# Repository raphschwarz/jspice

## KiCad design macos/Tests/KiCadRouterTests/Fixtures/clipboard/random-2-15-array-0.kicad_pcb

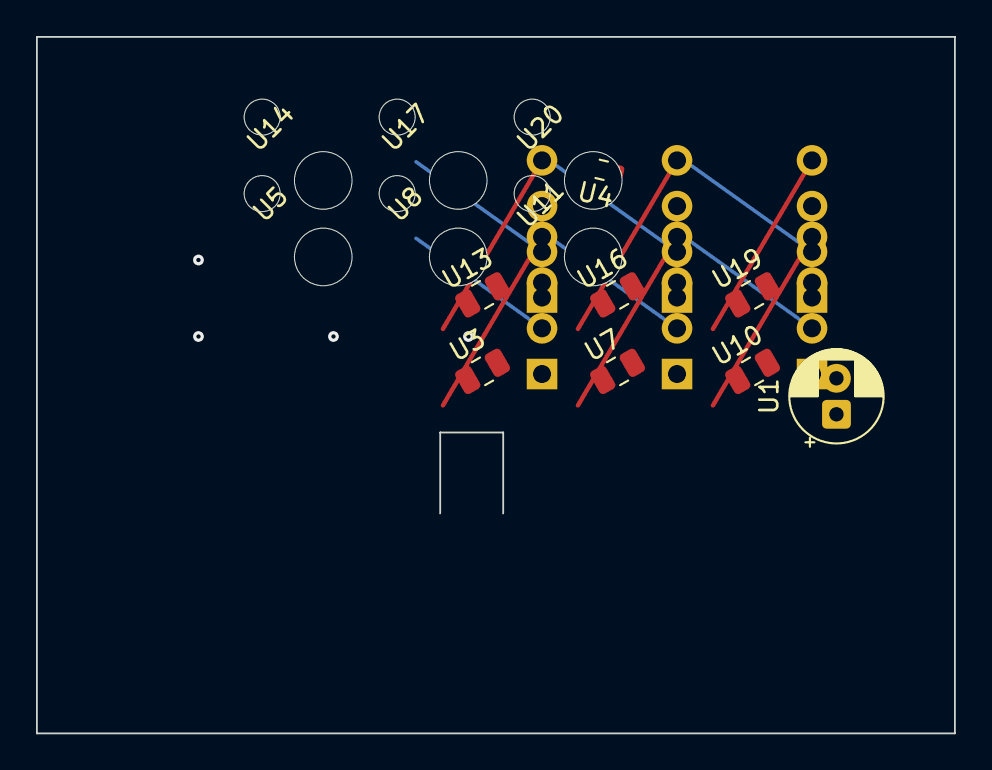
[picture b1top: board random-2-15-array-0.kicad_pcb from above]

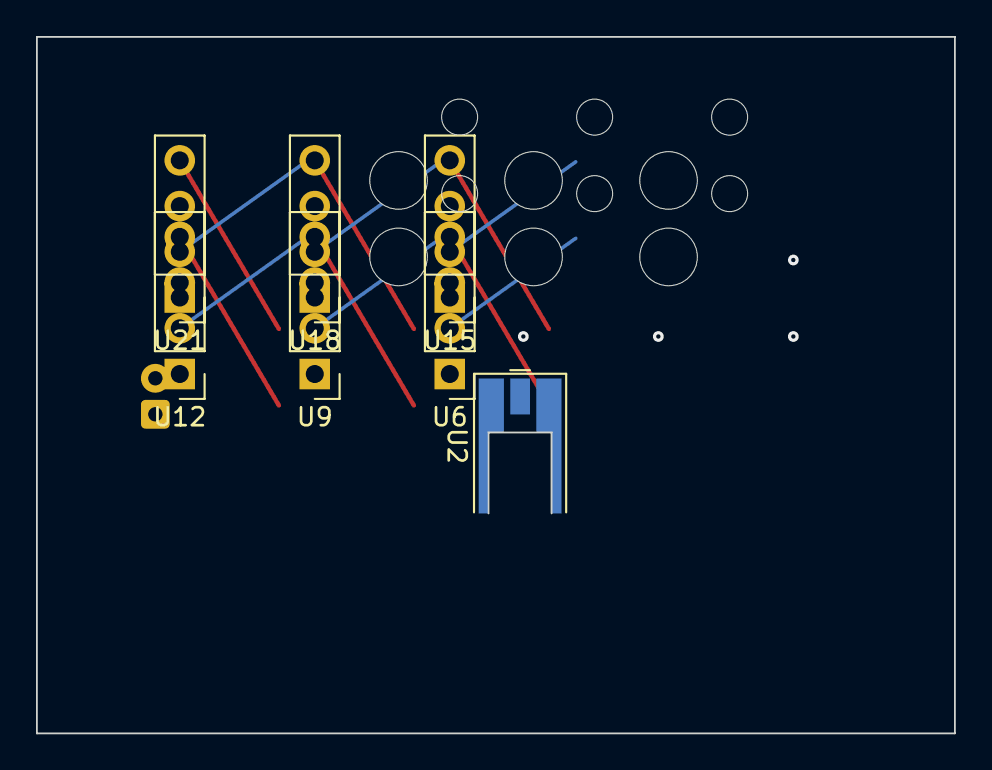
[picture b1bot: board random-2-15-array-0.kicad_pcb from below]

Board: 2 copper layers, 51.0 x 38.7 mm, 21 parts (7 on the bottom side), 2 nets.

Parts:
U1: CP_Radial_D5.0mm_P2.00mm
U2: MMCX_Molex_73415-0961_Horizontal_0.8mm-PCB
U3, U7, U10, U13, U16, U19: C_0805_2012Metric
U4: R_0603_1608Metric
U5, U8, U11, U14, U17, U20: MountingHole_3.2mm_M3
U6, U9, U12, U15, U18, U21: PinHeader_1x04_P2.54mm_Vertical

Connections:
N3: U1.1, U3.1, U6.1, U6.2, U7.1, U9.1, U9.2, U10.1, U12.1, U12.2, U13.1, U15.1, U15.2, U16.1, U18.1, U18.2, U19.1, U21.1, U21.2
PWR_5V: U6.3, U9.3, U12.3, U15.3, U18.3, U21.3

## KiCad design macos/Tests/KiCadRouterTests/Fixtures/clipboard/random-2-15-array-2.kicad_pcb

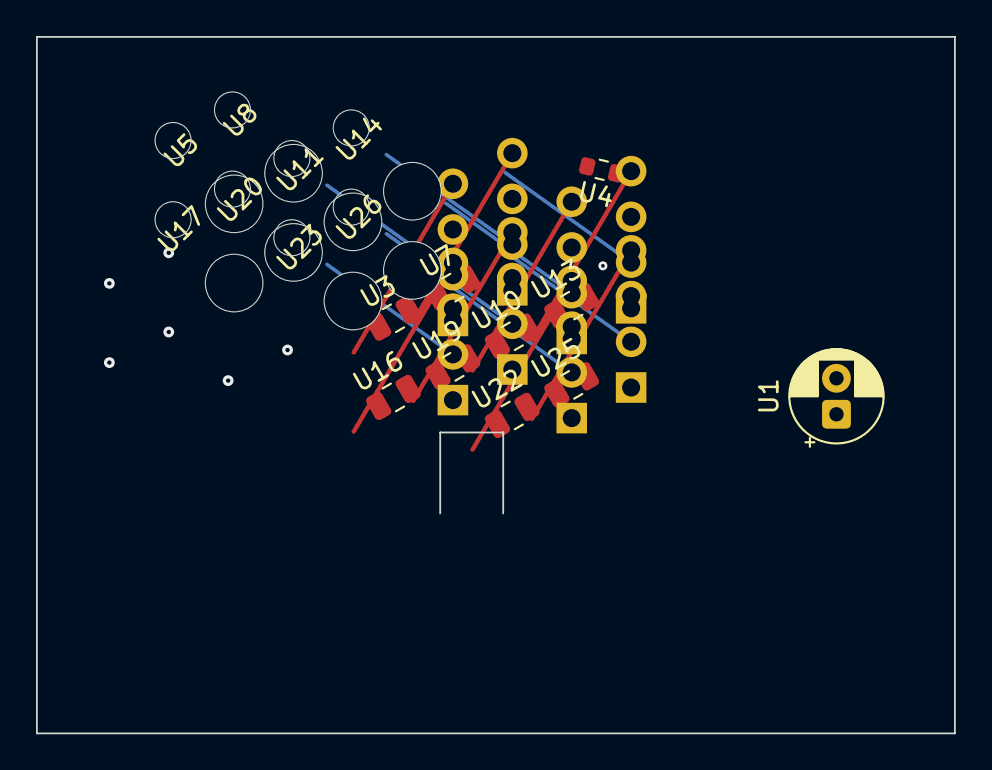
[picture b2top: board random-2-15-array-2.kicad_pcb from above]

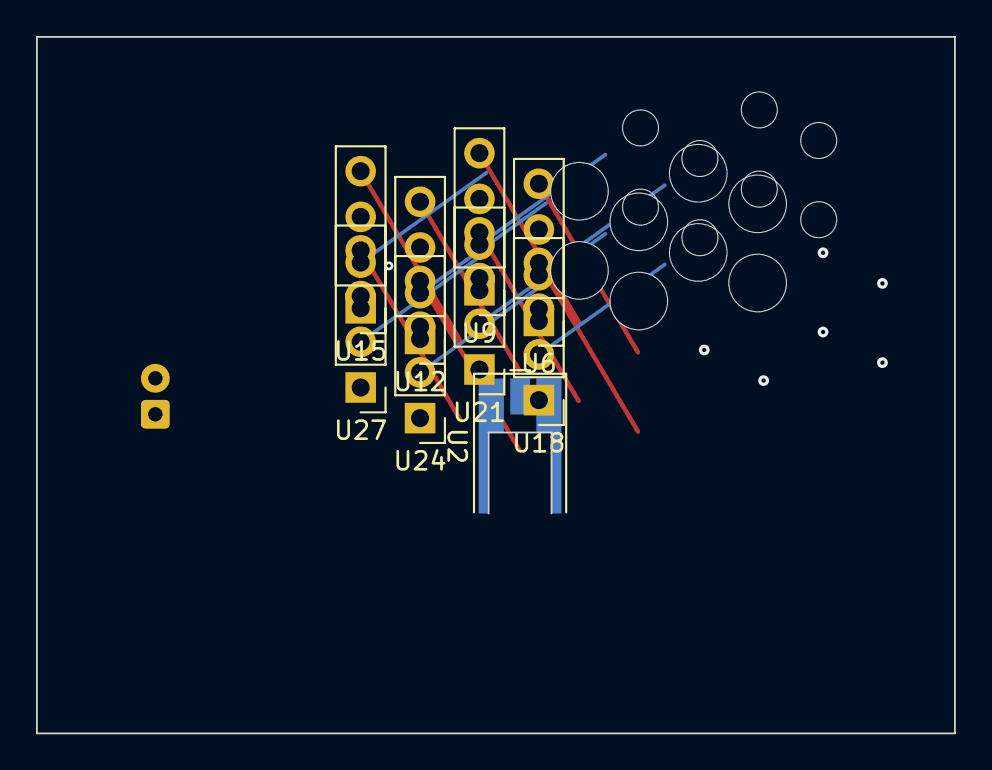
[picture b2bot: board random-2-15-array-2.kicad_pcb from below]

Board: 2 copper layers, 51.0 x 38.7 mm, 27 parts (9 on the bottom side), 2 nets.

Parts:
U1: CP_Radial_D5.0mm_P2.00mm
U2: MMCX_Molex_73415-0961_Horizontal_0.8mm-PCB
U3, U7, U10, U13, U16, U19, U22, U25: C_0805_2012Metric
U4: R_0603_1608Metric
U5, U8, U11, U14, U17, U20, U23, U26: MountingHole_3.2mm_M3
U6, U9, U12, U15, U18, U21, U24, U27: PinHeader_1x04_P2.54mm_Vertical

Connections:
N3: U1.1, U3.1, U6.1, U6.2, U7.1, U9.1, U9.2, U10.1, U12.1, U12.2, U13.1, U15.1, U15.2, U16.1, U18.1, U18.2, U19.1, U21.1, U21.2, U22.1, U24.1, U24.2, U25.1, U27.1, U27.2
PWR_5V: U6.3, U9.3, U12.3, U15.3, U18.3, U21.3, U24.3, U27.3
